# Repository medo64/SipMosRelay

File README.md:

SIP MOS Relay
-------------

High-voltage MOSFET-based switch in PhotoMOS footprint.

| Parameter              |     Min |     Nom |       Max |
|------------------------|--------:|--------:|----------:|
| Load voltage           |     8 V |         |      60 V |
| Continous load current |         |         |       6 A |
| Peak load current      |         |         |      11 A |
| Power dissipation      |         |         |       2 W |
| On-resistance          |         | 11.2 mΩ |   14.3 mΩ |
| Control input current  |         |  500 µA |           |
| Control current        |         |         |      2 mA |
| Thermal resistance     |         |         | 89.2 °C/W |
| Operating temperature  |  -40 °C |         |    +85 °C |

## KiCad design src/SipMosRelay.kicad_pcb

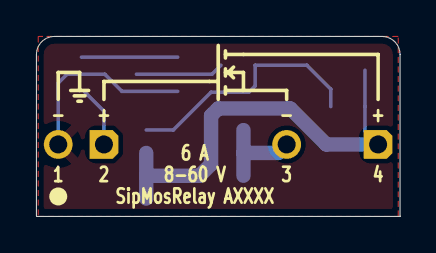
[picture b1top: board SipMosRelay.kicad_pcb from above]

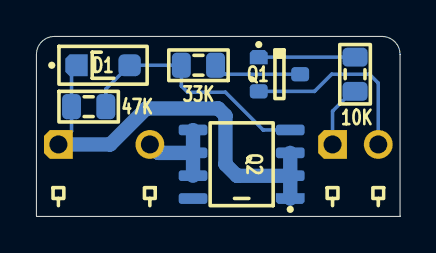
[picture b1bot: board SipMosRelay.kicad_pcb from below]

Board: 2 copper layers, 20.2 x 10.0 mm, 8 parts (8 on the bottom side), 7 nets.

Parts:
D1: BZT52C12; D Zener (SOD123FL)
J1: J Header (2w)
J2: J Header (3-2w)
Q1: BC846B,235; Q Transistor NPN (SOT23-3)
Q2: RS3L110ATTB1; Q MOSFET-P (SO-8)
R1: 10K; R (0805)
R2: 33K; R (0805)
R3: 47K; R (0805)

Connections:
BASE: Q1.1, R1.2
COLLECTOR: Q1.3, R2.1
CONTROL: J1.1, R1.1
GATE: D1.2, Q2.4, R2.2, R3.2
GND: J1.2, Q1.2
INPUT: D1.1, J2.1, Q2.1, Q2.2, Q2.3, R3.1
OUTPUT: J2.3, Q2.5, Q2.6, Q2.7
